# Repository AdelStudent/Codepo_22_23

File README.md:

## Contents
- `main`: Code for Arduino
- `esp32_easy`: Code for ESP32
- `PCD codepo`: Used to share progress on the PCB
- `Report_final`: Used for writing monthly reports (code to transfer to Arduino)
- `projet codepo`: Used for reading different sensors (code to transfer to Arduino)
- `PythonTest`: Code permettant de vérifier l'envoie de message via le broker Thingstream
- `Modélisation Congo`: Modèle permettant de prédire la consommation en énergie de la cameskin
- `Data Type Cameskin`: Dossier que la CAMESKIN nous a partagé afin comparer si nos moyens de communiquer la data est pertinante

Voici quelques commandes git utiles:

### Download the project
- git clone https://github.com/AdelStudent/Codepo_22_23.git

### Update a downloaded code
- git status
- git pull

### Commit a new code!!
- git add .
- git commit -a -m "Update Message"
- git push

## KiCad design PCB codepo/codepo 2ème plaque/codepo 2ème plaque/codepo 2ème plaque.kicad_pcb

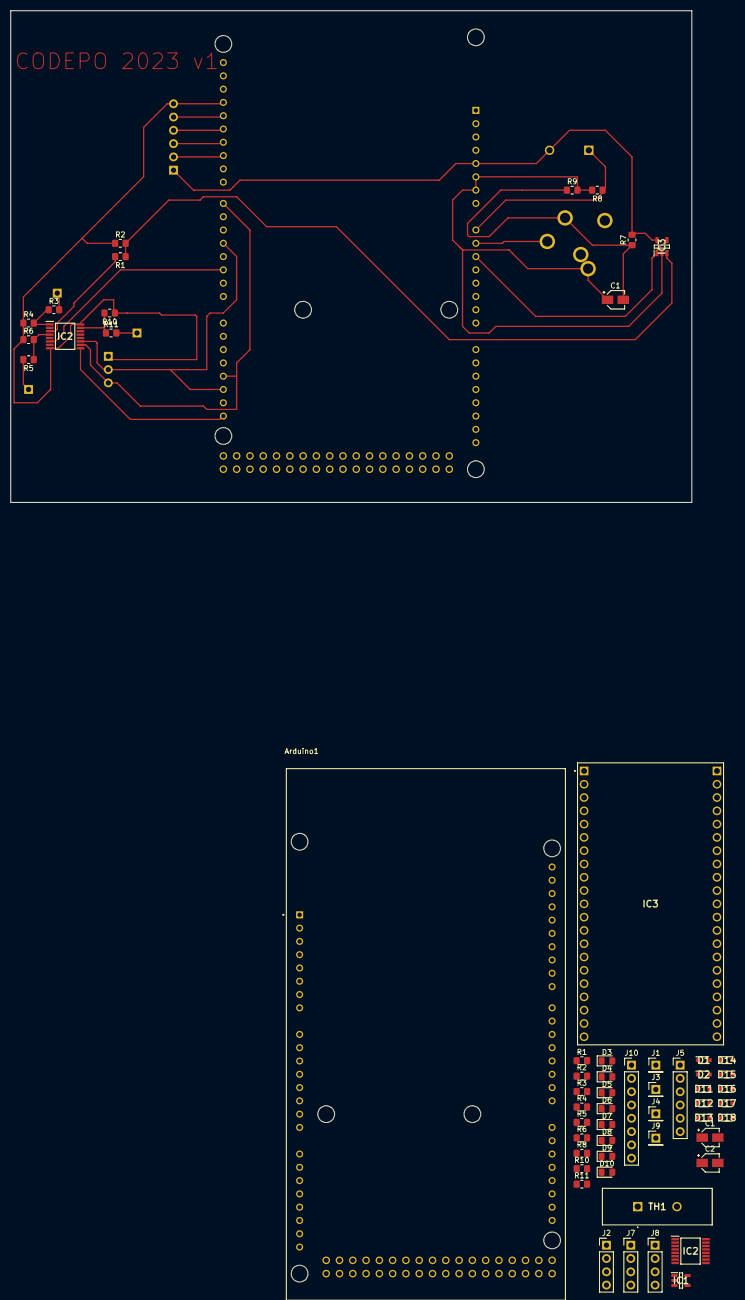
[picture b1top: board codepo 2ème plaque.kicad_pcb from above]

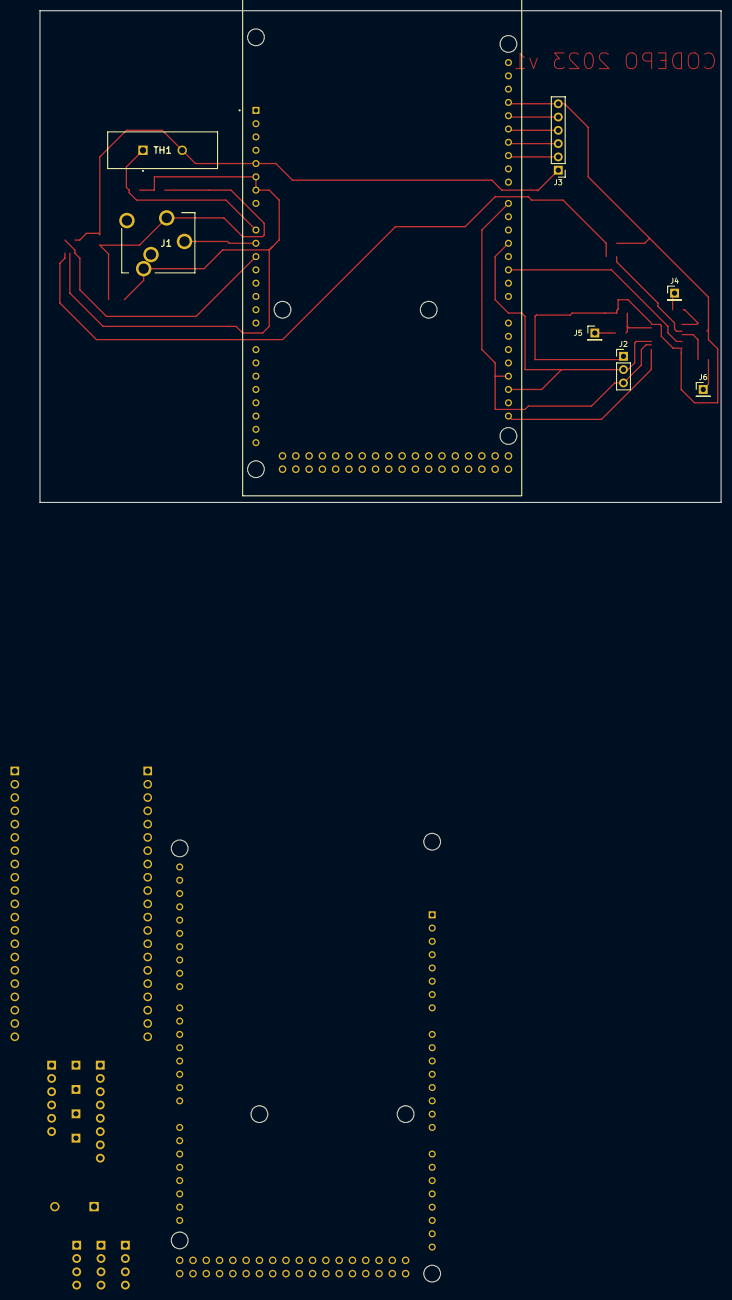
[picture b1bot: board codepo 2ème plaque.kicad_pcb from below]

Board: 2 copper layers, 130.2 x 94.0 mm, 65 parts (8 on the bottom side), 27 nets.

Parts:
Arduino1, Arduino1#2: DUE; MODULE_A000062
C1: 100 uF; CP_Elec_3x5.3
C1#2, C2: 0.1uF; CP_Elec_3x5.3
D1, D2, D11, D12, D13, D14, D15, D16, D17, D18: D_Schottky; SODFL2513X70N
D3, D4, D5, D6, D7, D8, D9, D10: D_Zener; D_0805_2012Metric_Pad1.15x1.40mm_HandSolder
IC1, IC3: OPA182IDBVR; SOT95P280X145-5N
IC2, IC2#2: TMUX4051PWR; SOP65P640X120-16N
IC3#2: ESP32-S2-Saola-1RI; ESP32S2Saola1RI
J1, J3, J4, J4#2, J5#2, J6, J9: Conn_01x01_Pin; PinHeader_1x01_P2.54mm_Vertical
J1#2: 35RAPC4BH3
J2, J7, J8: Conn_01x04_Pin; PinHeader_1x04_P2.54mm_Vertical
J2#2: Conn_01x03_Pin; PinHeader_1x03_P2.54mm_Vertical
J3#2, J5: Conn_01x06_Pin; PinHeader_1x06_P2.54mm_Vertical
J10: Conn_01x08_Pin; PinHeader_1x08_P2.54mm_Vertical
R1, R1#2: 910kohm; R_0805_2012Metric_Pad1.20x1.40mm_HandSolder
R2, R2#2: 270kohm; R_0805_2012Metric_Pad1.20x1.40mm_HandSolder
R3, R3#2, R10, R10#2, R11, R11#2: 910Kohm; R_0805_2012Metric_Pad1.20x1.40mm_HandSolder
R4, R4#2: 450kohm; R_0805_2012Metric_Pad1.20x1.40mm_HandSolder
R5, R5#2: 910 kohms; R_0805_2012Metric_Pad1.20x1.40mm_HandSolder
R6, R6#2: 300kohm; R_0805_2012Metric_Pad1.20x1.40mm_HandSolder
R7, R8, R8#2, R9: 10kohm; R_0805_2012Metric_Pad1.20x1.40mm_HandSolder
TH1, TH1#2: Thermistor_NTC; B57364S0300M000

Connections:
0: Arduino1.GND1, Arduino1.GND2, C1#2.1, D1.1 (K), D2.1 (K), D3.2 (A), D4.2 (A), D5.2 (A), D6.2 (A), D7.2 (A), D8.2 (A), D9.2 (A), D10.2 (A), D11.1 (K), D12.1 (K), D13.1 (K), D14.1 (K), D15.1 (K), D16.1 (K), D17.1 (K), D18.1 (K), IC1.2 (V-), IC2#2.2 (S6), IC2#2.5 (S5), IC2#2.8 (GND), IC2#2.14 (S1), IC3#2.22 (GND_2), J2.1, J5.6, J7.1, J8.1, J10.8, R2.1, R4#2.1, R6#2.1, R8.2, R10.1
5V: Arduino1.5V_1 (+5V_1), C2.1, J2.4, J5.5, J7.4, J8.4, TH1.2
unnamed: Arduino1.AD0 (ADC0), D3.1 (K), R8.1, TH1.1
unnamed: Arduino1.AD1 (ADC1), D4.1 (K), IC1.1 (OUT), IC1.4 (-IN)
unnamed: Arduino1.AD2 (ADC2), D5.1 (K), J2.2
unnamed: Arduino1.AD3 (ADC3), D6.1 (K), J2.3
unnamed: Arduino1.AD4 (ADC4), D7.1 (K), J8.2
unnamed: Arduino1.AD5 (ADC5), D8.1 (K), J8.3
unnamed: Arduino1.AD6 (ADC6), D9.1 (K), J7.2
unnamed: Arduino1.AD7 (ADC7), D10.1 (K), J7.3
unnamed: Arduino1.2 (D2), D11.2 (A), IC2#2.6 (~EN)
unnamed: Arduino1.16 (D16/TX2), D12.2 (A), IC3#2.26 (U0RXD)
unnamed: Arduino1.17 (D17/RX2), D13.2 (A), IC3#2.25 (GPIO45)
unnamed: Arduino1.7 (D7), Arduino1.18 (D18/TX1), Arduino1.21 (D21/SCL), D1.2 (A), D14.2 (A), D16.2 (A), IC2#2.9 (A2), IC2#2.10 (A1), J10.4
unnamed: Arduino1.4 (D4), Arduino1.19 (D19/RX1), D2.2 (A), D15.2 (A), IC2#2.11 (A0), J10.3
unnamed: Arduino1.52 (D52), D17.2 (A), J5.1
unnamed: D18.2 (A), IC1.3 (+IN), R1#2.1, R2.2
unnamed: C2.2, IC1.5 (V+)
unnamed: IC2#2.3 (D), R1#2.2
unnamed: IC2#2.15 (S2), R10.2, R11.1
unnamed: IC2#2.12 (S3), J9.1
unnamed: IC2#2.1 (S4), R3#2.1, R4#2.2
unnamed: IC2#2.4 (S7), R5.1, R6#2.2
unnamed: C1#2.2, IC2#2.16 (VDD)
unnamed: J1.1, R5.2
unnamed: J3.1, R3#2.2
unnamed: J4.1, R11.2

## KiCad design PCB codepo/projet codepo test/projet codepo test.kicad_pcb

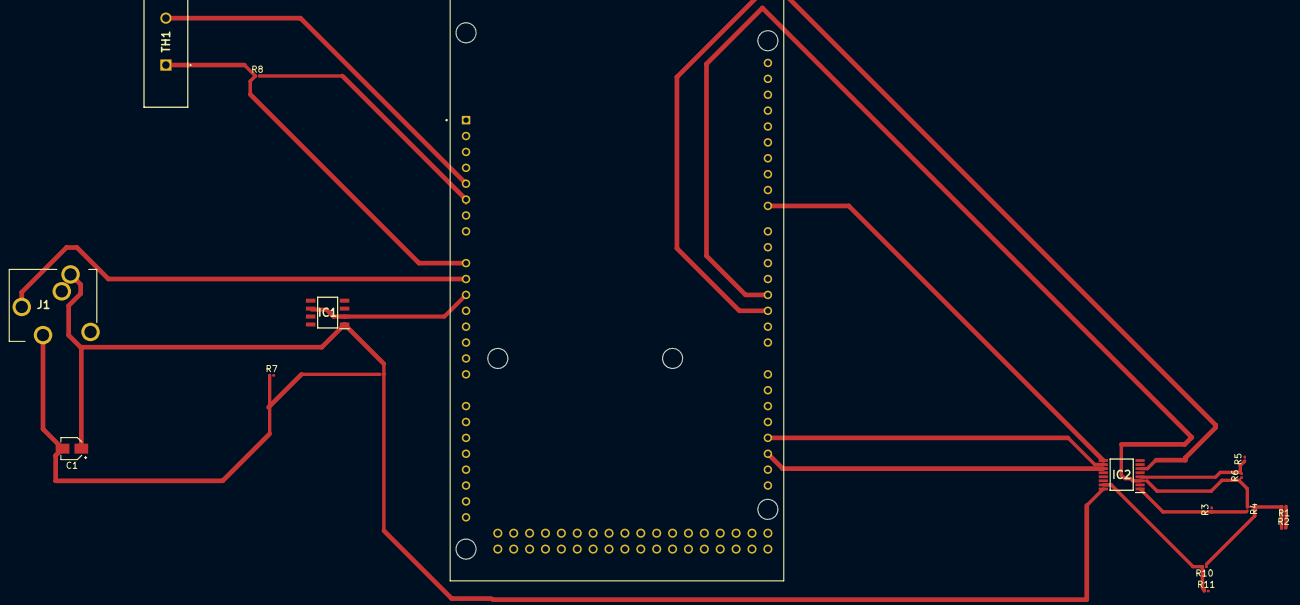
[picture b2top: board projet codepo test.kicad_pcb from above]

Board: 2 copper layers, 17 parts (0 on the bottom side), 15 nets.

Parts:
Arduino1: DUE; MODULE_A000062
C1: 100 uF; CP_Elec_3x5.3
IC1: OPA182IDR; SOIC127P600X175-8N
IC2: TMUX4051PWR; SOP65P640X120-16N
J1: 35RAPC4BH3
R1: 910kohm; R_0201_0603Metric
R2: 270kohm; R_0201_0603Metric
R3, R10, R11: 910Kohm; R_0201_0603Metric
R4: 450kohm; R_0201_0603Metric
R5: 910 kohms; R_0201_0603Metric
R6: 300kohm; R_0201_0603Metric
R7, R8, R9: 10kohm; R_0201_0603Metric
TH1: Thermistor_NTC; B57364S0300M000

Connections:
0: Arduino1.3 (D3), IC2.3 (D), R1.2, R2.1, R4.1, R6.1, R10.1
unnamed: Arduino1.5V_1 (+5V_1), IC1.8 (V+), R7.2, TH1.2
unnamed: Arduino1.AD0 (ADC0), R8.1, TH1.1
unnamed: Arduino1.AD1 (ADC1), J1.1
unnamed: Arduino1.AD2 (ADC2), IC1.2 (-IN_A), IC1.6 (-IN_B)
unnamed: Arduino1.2 (D2), IC2.6 (~EN)
unnamed: Arduino1.8 (D8), IC2.9 (A2)
unnamed: Arduino1.7 (D7), Arduino1.18 (D18/TX1), IC2.10 (A1)
unnamed: Arduino1.4 (D4), Arduino1.19 (D19/RX1), IC2.11 (A0)
unnamed: C1.2, J1.5, R7.1, R9.1
unnamed: Arduino1.GND1, C1.1, IC1.1 (OUT_A), IC2.8 (GND), IC2.16 (VDD), J1.2, R8.2, R9.2
unnamed: IC2.15 (S2), R10.2, R11.1
unnamed: IC2.1 (S4), R3.1, R4.2
unnamed: IC2.4 (S7), R5.1, R6.2
unnamed: R1.1, R2.2

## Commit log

2023-04-29 Update measure.ino
    Merge de la branche measure
2023-05-05 Rajout d'une condition
    Si on a une valeur pour le courant supérieur à 30A, ce n'est pas bon non plus. -> On le fais égaler à 0. On pourrait le mettre sous forme de texte "Overload" mais cela rentrerait créerait pe un confl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
2023-07-07 Add files via upload
    Checking periodically if the ESP32 got disconnected to the Wifi.
2023-07-08 Update measure.ino
    Changement des valeurs des résistances
2023-07-08 Vcc Tension
2023-07-08 Réajustement des résistances
2023-07-10 Nouvel fonction de mesure de courant
2023-07-10 Constantes pour le capteur de courant
2023-07-11 Update all_constant2.h OFFSET COURANT
2023-07-11 COURANT measure.ino
2023-07-12 courant all_constant2.h
2023-07-12 Ajout Modèle
2023-07-13 test
2023-07-13 Resistance des diviseurs résistifs measure.ino
2023-07-13 Arduino answering_mode + corrections
2023-07-13 Bug de synchro corrigée
2023-07-13 Readme Update
2023-07-14 Résolution Bug ReportWriting()
2023-07-14 REPORT DEBUGGING
2023-07-14 Ajout du bouton 'Courant Reseau'
2023-07-14 Mini Refactor
2023-07-16 Ajout du dossier 'Data Type Cameskin'
2023-07-16 Add files via upload
    Ajout du dossier 'Data Type Cameskin'
2023-07-17 Function Test Calibration
    Fonction permettant d'afficher ce qu'il se passe sur le réseau au niveau courant
2023-07-17 ACmesure measure.ino
2023-07-18 Ajout test thingstream
2023-07-18 ajout thingstream test
2023-07-18 Modif Pour ESP32 LocalTime
2023-07-18 Thingstream Warning Functions Start
2023-07-18 Update README.md
    Ajout du dossier PythonTest
2023-07-19 Update Simple
2023-07-19 tension batterie par batterie.ino
2023-07-20 Modif Thingstream
2023-07-20 Ajout details
2023-07-21 Ajout RTC DS3231
2023-07-23 Add DS3231 Functions
2023-07-24 Update DS3231
2023-07-24 SOC Kalman
2023-07-24 Ajout Kalman
2023-07-25 Finaliser Thingstream
2023-07-26 DS3231
2023-07-26 Synchronisation Hardware-Software
2023-07-28 Version beta
2023-07-31 LAST VERSION
